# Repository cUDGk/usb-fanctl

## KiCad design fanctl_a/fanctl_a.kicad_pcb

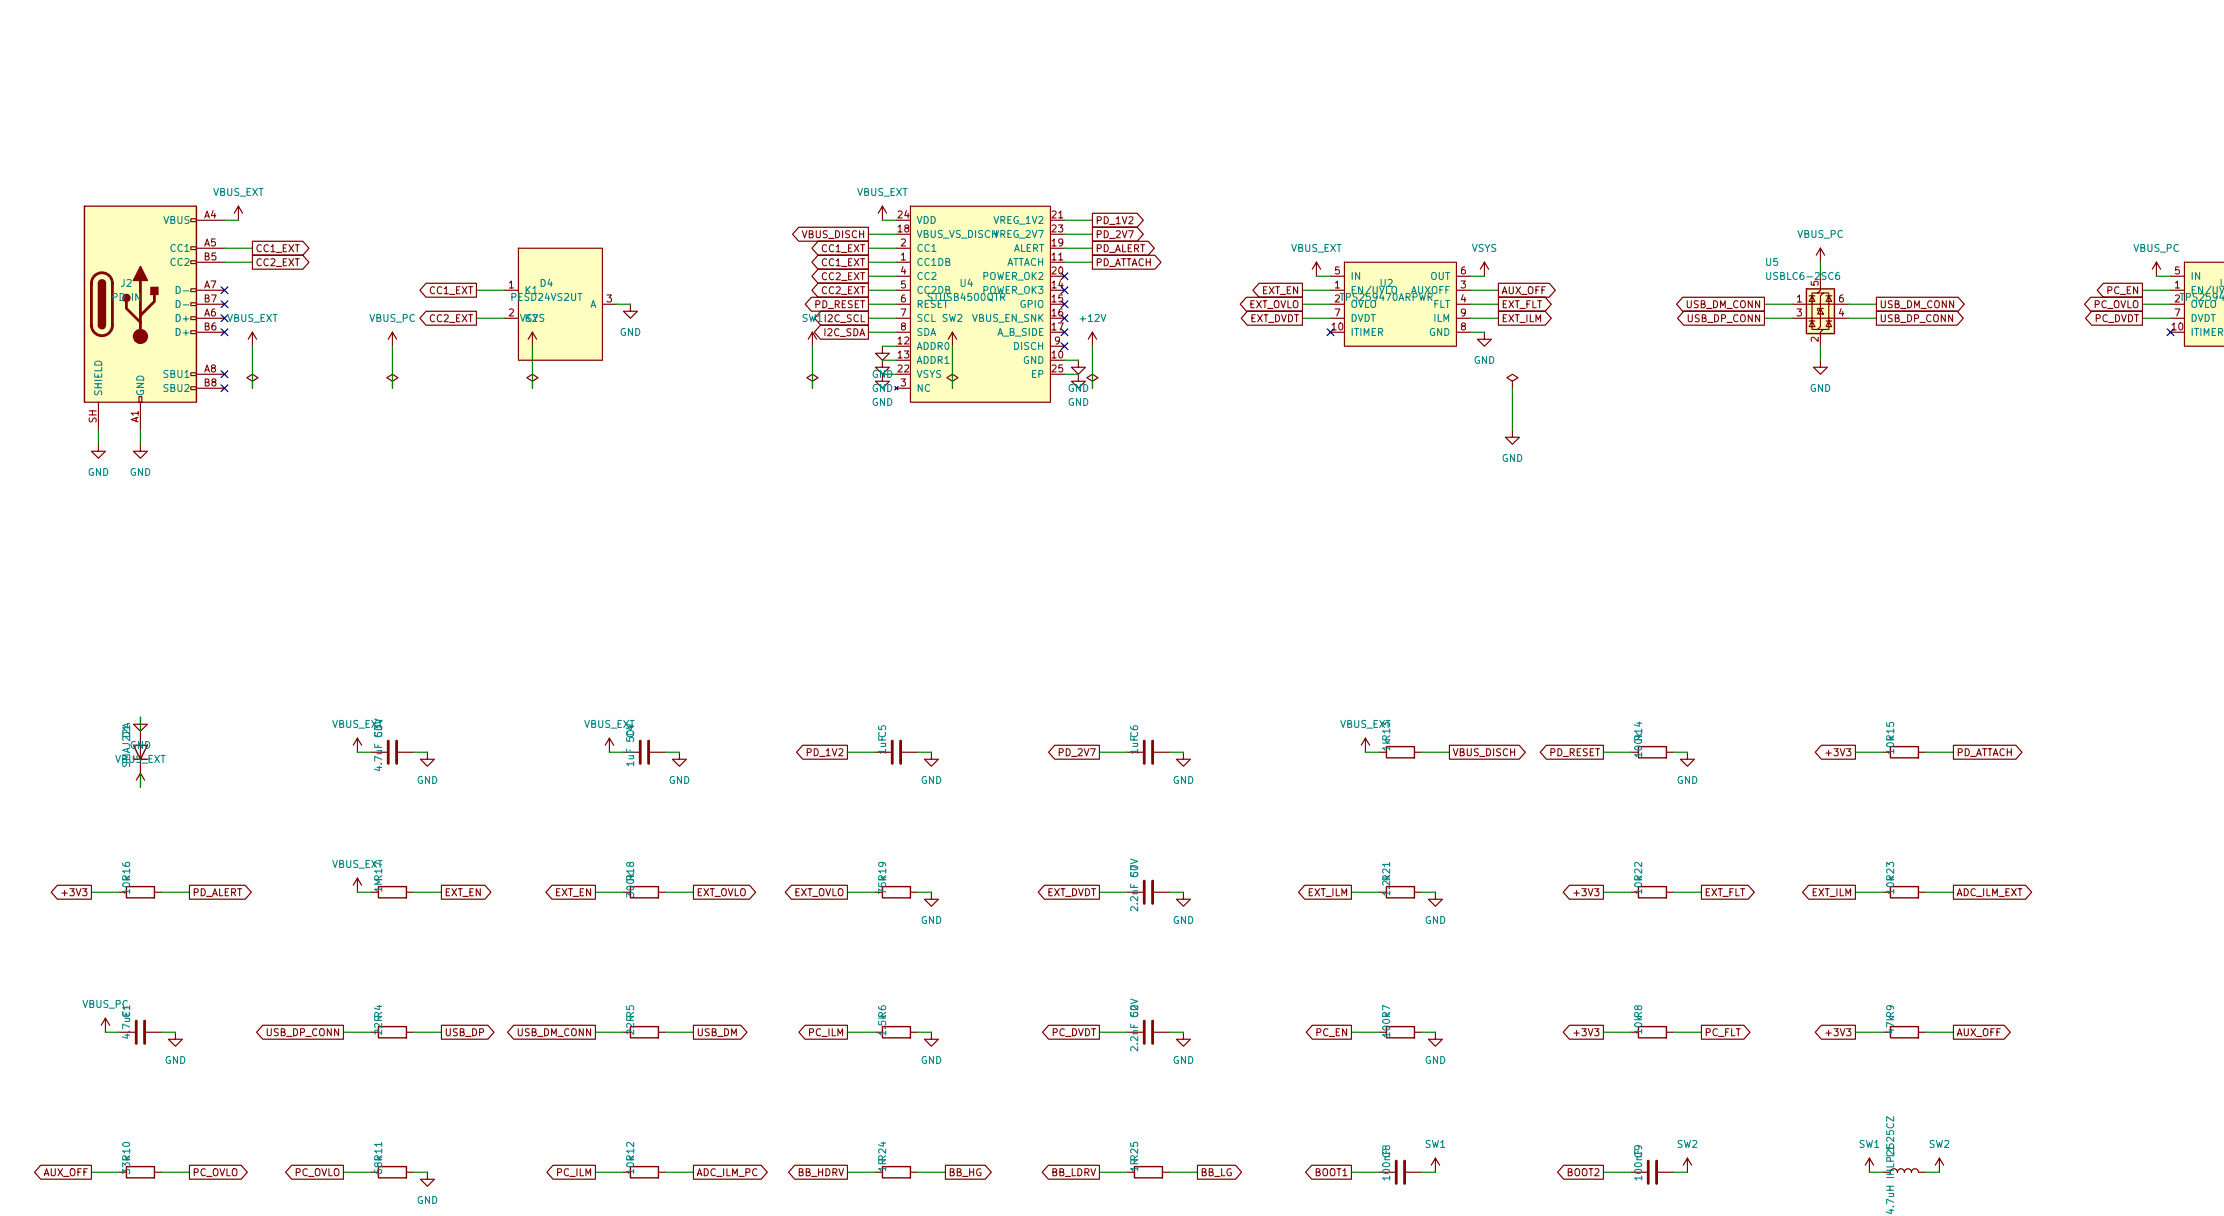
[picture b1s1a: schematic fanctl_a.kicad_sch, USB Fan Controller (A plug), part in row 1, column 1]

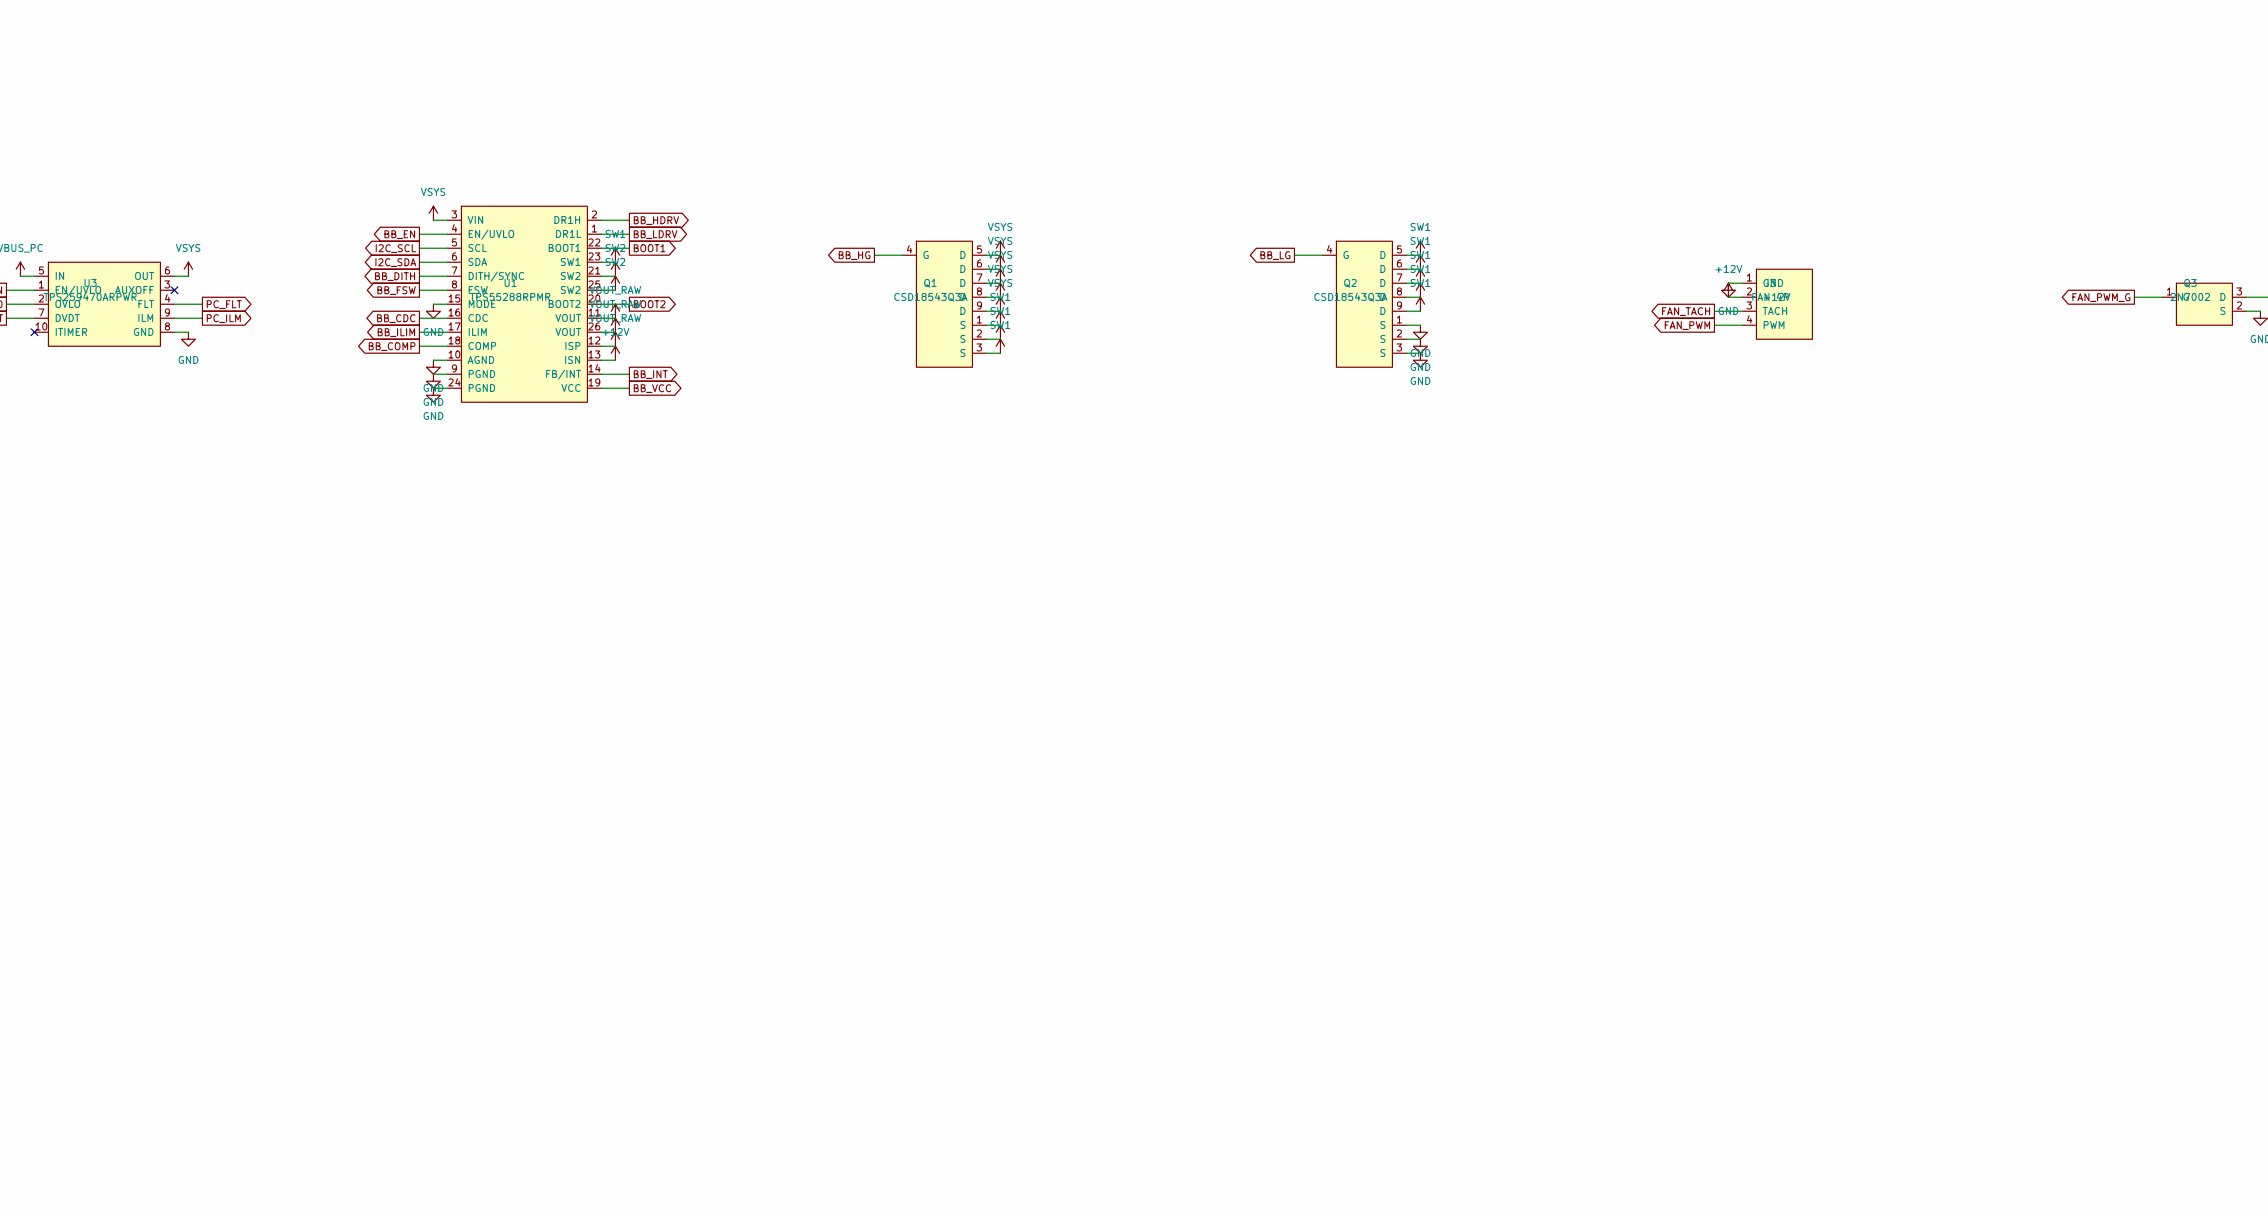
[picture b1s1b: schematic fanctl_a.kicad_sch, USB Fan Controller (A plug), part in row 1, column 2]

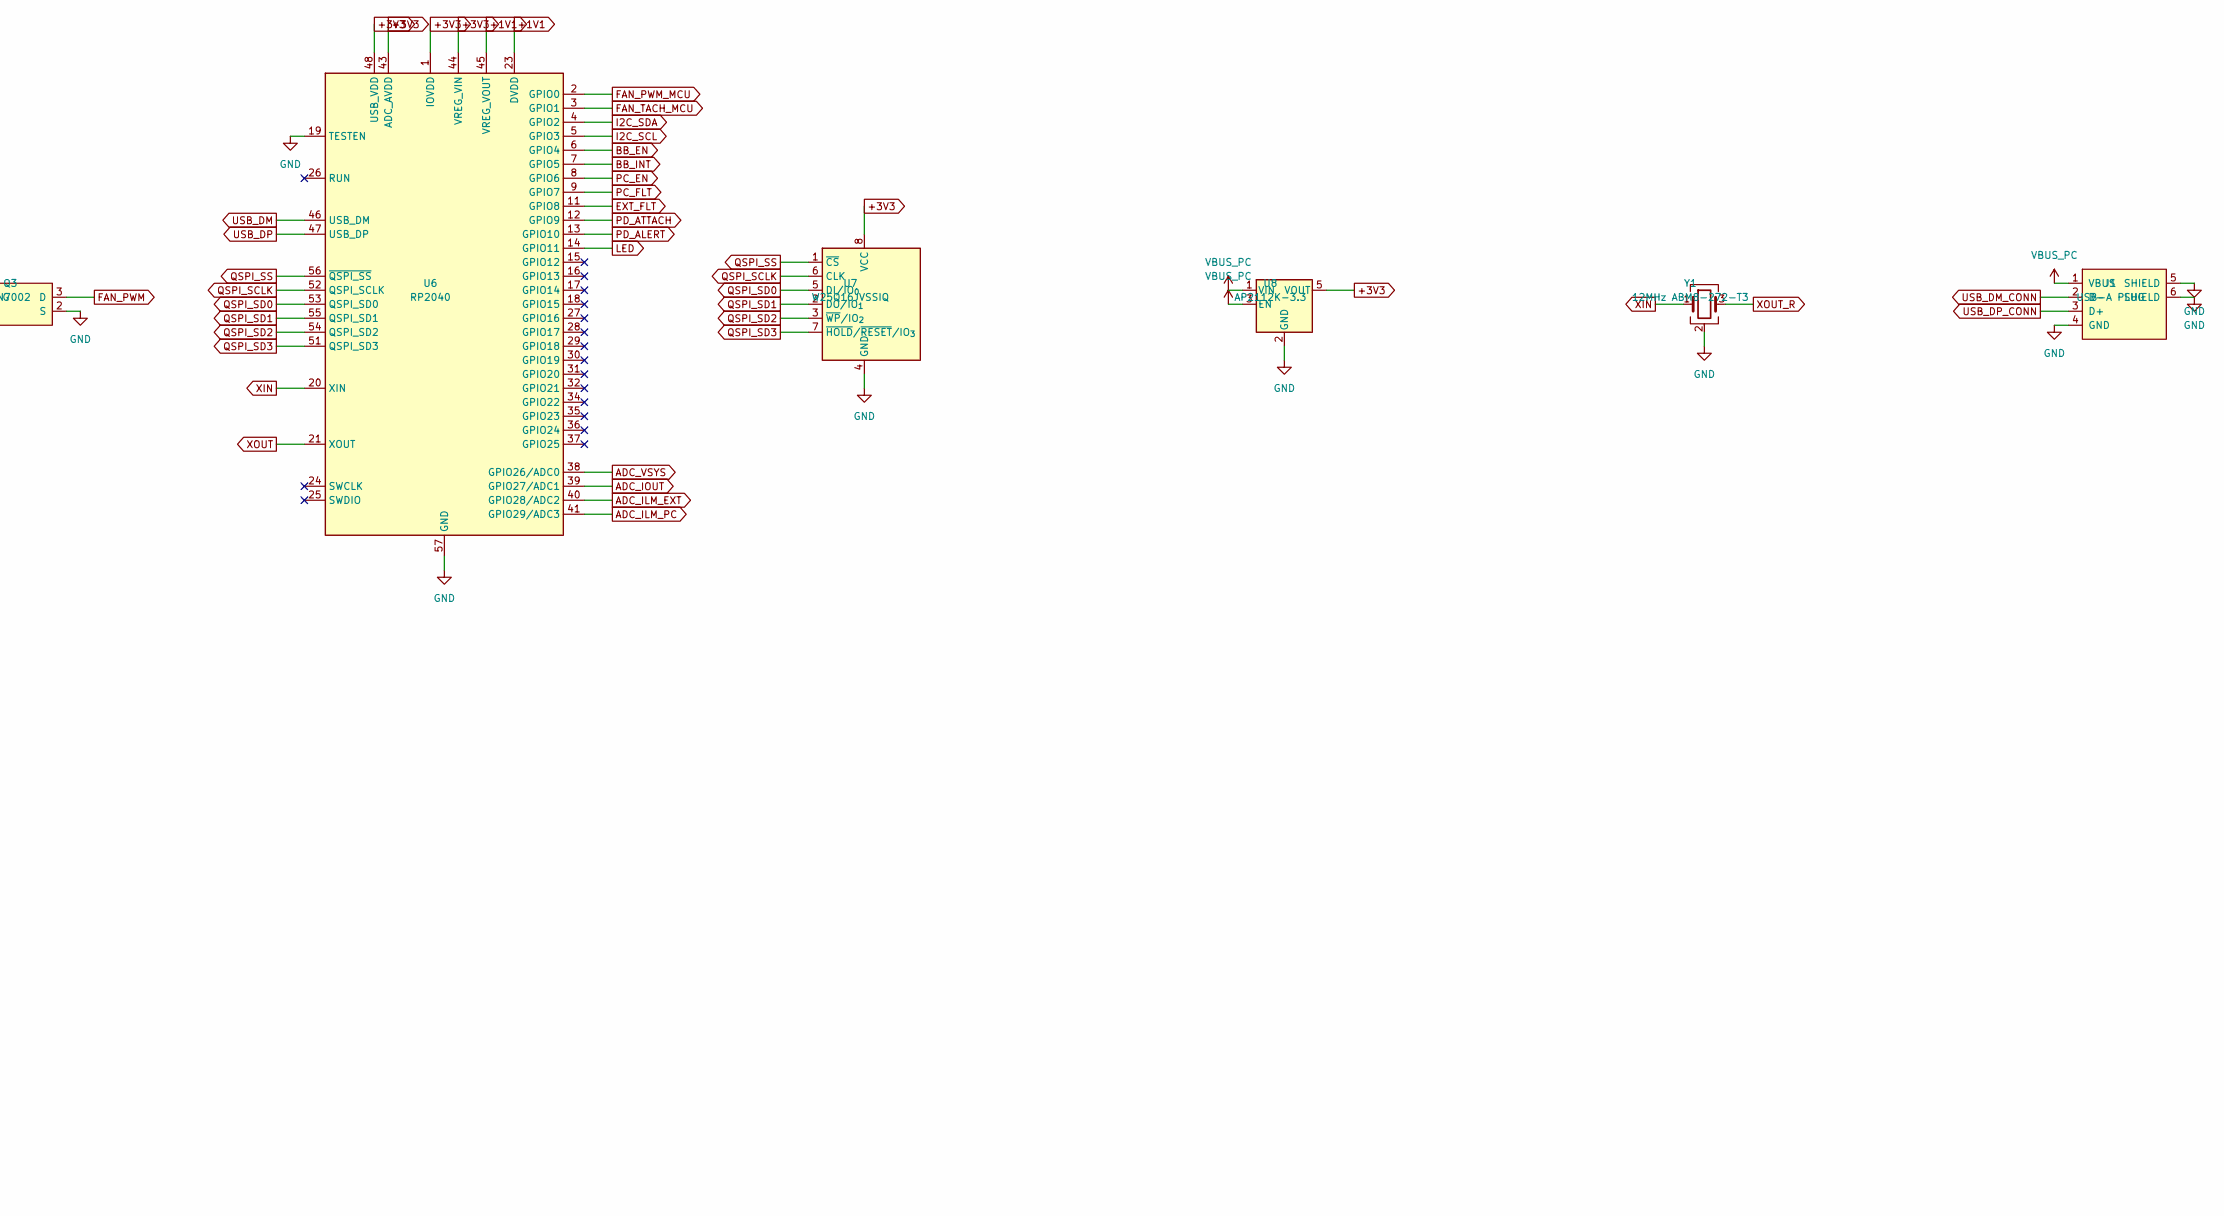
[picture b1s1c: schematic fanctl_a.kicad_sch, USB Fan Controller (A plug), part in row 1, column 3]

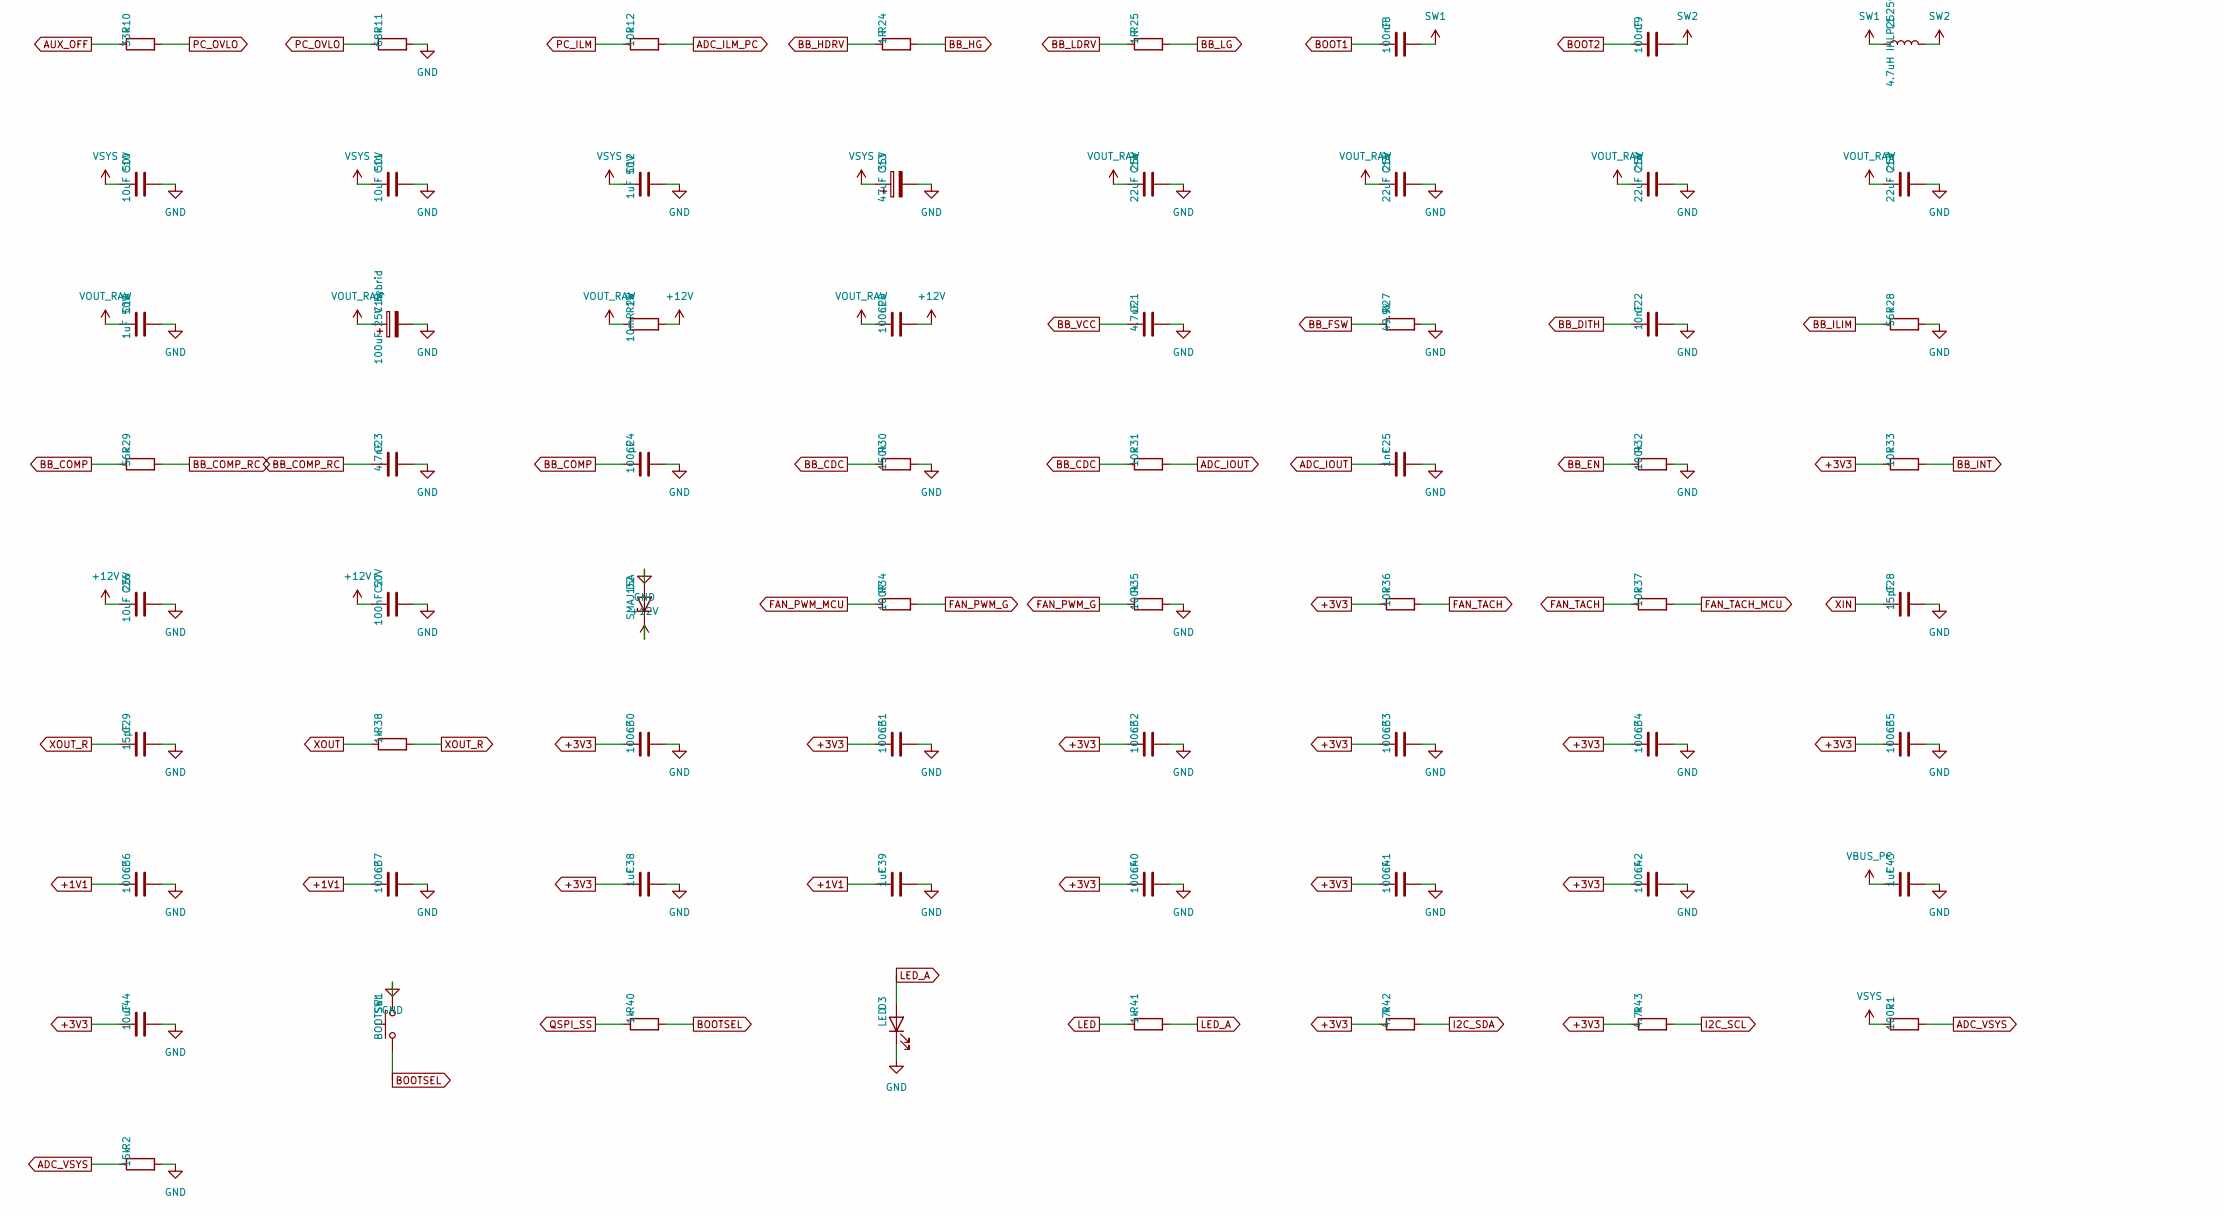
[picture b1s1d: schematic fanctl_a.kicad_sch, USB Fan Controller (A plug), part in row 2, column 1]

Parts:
C1, C21: 4.7uF; C_0603_1608Metric
C2, C7: 2.2nF 50V; C_0402_1005Metric
C3: 4.7uF 50V; C_1206_3216Metric
C4, C12, C18: 1uF 50V; C_0603_1608Metric
C5, C6, C38, C39, C43: 1uF; C_0402_1005Metric
C8, C9, C20, C30, C31, C32, C33, C34, C35, C36, C37, C40, C41, C42: 100nF; C_0402_1005Metric
C10, C11: 10uF 50V; C_1206_3216Metric
C13: 47uF 35V; CP_Elec_6.3x5.4
C14, C15, C16, C17: 22uF 25V; C_1206_3216Metric
C19: 100uF 25V hybrid; CP_Elec_6.3x5.8
C22: 10nF; C_0402_1005Metric
C23: 4.7nF; C_0402_1005Metric
C24: 100pF; C_0402_1005Metric
C25: 1nF; C_0402_1005Metric
C26: 10uF 25V; C_0805_2012Metric
C27: 100nF 50V; C_0402_1005Metric
C28, C29: 15pF; C_0402_1005Metric
C44: 10uF; C_0603_1608Metric
D1: SMAJ22A; D_SMA
D2: SMAJ15A; D_SMA
D3: LED; LED_0603_1608Metric
D4: PESD24VS2UT; SOT-23
J1: USB-A PLUG; USB-A-TH_USB2.0-A90-G
J2: PD IN; USB_C_Receptacle_HRO_TYPE-C-31-M-12
J3: FAN 4P; FanPinHeader_1x04_P2.54mm_Vertical
L1: 4.7uH IHLP2525CZ; L_Vishay_IHLP-2525
Q1, Q2: CSD18543Q3A; VSONP-8_L3.1-W3.1-P0.65-LS3.5-BL
Q3: 2N7002; SOT-23
R1, R7, R14, R32, R35: 100k; R_0402_1005Metric
R2: 15k; R_0402_1005Metric
R4, R5: 22R; R_0402_1005Metric
R6: 1.5k; R_0402_1005Metric
R8, R12, R15, R16, R22, R23, R31, R33, R36, R37: 10k; R_0402_1005Metric
R9: 47k; R_0402_1005Metric
R10: 33k; R_0402_1005Metric
R11: 68k; R_0402_1005Metric
R13: 1k; R_0805_2012Metric
R17: 1M; R_0402_1005Metric
R18: 300k; R_0402_1005Metric
R19: 75k; R_0402_1005Metric
R21: 1.2k; R_0402_1005Metric
R24, R25: 1R; R_0402_1005Metric
R26: 10mR 1W; R_1206_3216Metric
R27: 49.9k; R_0402_1005Metric
R28, R29: 56k; R_0402_1005Metric
R30: 150k; R_0402_1005Metric
R34: 100R; R_0402_1005Metric
R38, R40, R41: 1k; R_0402_1005Metric
R42, R43: 4.7k; R_0402_1005Metric
SW1: BOOTSEL; SW-SMD_4P-L5.1-W5.1-P3.70-LS6.5-TL_H1.5
U1: TPS55288RPMR; VQFN-HR-26_L4.0-W3.5_TPS55288RPMR
U2, U3: TPS259470ARPWR; VQFN-10_L2.0-W2.0-P0.45-TL
U4: STUSB4500QTR; QFN-24_L4.0-W4.0-P0.50-BL-EP2.8
U5: USBLC6-2SC6; SOT-23-6
U6: RP2040; QFN-56-1EP_7x7mm_P0.4mm_EP3.2x3.2mm
U7: W25Q16JVSSIQ; SOIC-8_5.3x5.3mm_P1.27mm
U8: AP2112K-3.3; SOT-23-5
Y1: 12MHz ABM8-272-T3; Crystal_SMD_3225-4Pin_3.2x2.5mm

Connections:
+1V1: C36.1, C37.1, C39.1, U6.23 (DVDD), U6.45 (VREG_VOUT), U6.50 (DVDD)
+3V3: C30.1, C31.1, C32.1, C33.1, C34.1, C35.1, C38.1, C40.1, C41.1, C42.1, C44.1, R8.1, R9.1, R15.1, R16.1, R22.1, R33.1, R36.1, R42.1, R43.1, U6.1 (IOVDD), U6.10 (IOVDD), U6.22 (IOVDD), U6.33 (IOVDD), U6.42 (IOVDD), U6.43 (ADC_AVDD), U6.44 (VREG_VIN), U6.48 (USB_VDD), U6.49 (IOVDD), U7.8 (VCC), U8.5 (VOUT)
+12V: C20.2, C26.1, C27.1, D2.1 (K), J3.2 (+12V), R26.2, U1.13 (ISN)
ADC_ILM_EXT: R23.2, U6.40 (GPIO28/ADC2)
ADC_ILM_PC: R12.2, U6.41 (GPIO29/ADC3)
ADC_IOUT: C25.1, R31.2, U6.39 (GPIO27/ADC1)
ADC_VSYS: R1.2, R2.1, U6.38 (GPIO26/ADC0)
AUX_OFF: R9.2, R10.1, U2.3 (AUXOFF)
BB_CDC: R30.1, R31.1, U1.16 (CDC)
BB_COMP: C24.1, R29.1, U1.18 (COMP)
BB_COMP_RC: C23.1, R29.2
BB_DITH: C22.1, U1.7 (DITH/SYNC)
BB_EN: R32.1, U1.4 (EN/UVLO), U6.6 (GPIO4)
BB_FSW: R27.1, U1.8 (FSW)
BB_HDRV: R24.1, U1.2 (DR1H)
BB_HG: Q1.4 (G), R24.2
BB_ILIM: R28.1, U1.17 (ILIM)
BB_INT: R33.2, U1.14 (FB/INT), U6.7 (GPIO5)
BB_LDRV: R25.1, U1.1 (DR1L)
BB_LG: Q2.4 (G), R25.2
BB_VCC: C21.1, U1.19 (VCC)
BOOT1: C8.1, U1.22 (BOOT1)
BOOT2: C9.1, U1.20 (BOOT2)
BOOTSEL: R40.2, SW1.1
CC1_EXT: D4.1 (K1), J2.A5 (CC1), U4.1 (CC1DB), U4.2 (CC1)
CC2_EXT: D4.2 (K2), J2.B5 (CC2), U4.4 (CC2), U4.5 (CC2DB)
EXT_DVDT: C7.1, U2.7 (DVDT)
EXT_EN: R17.2, R18.1, U2.1 (EN/UVLO)
EXT_FLT: R22.2, U2.4 (FLT), U6.11 (GPIO8)
EXT_ILM: R21.1, R23.1, U2.9 (ILM)
EXT_OVLO: R18.2, R19.1, U2.2 (OVLO)
FAN_PWM: J3.4 (PWM), Q3.3 (D)
FAN_PWM_G: Q3.1 (G), R34.2, R35.1
FAN_PWM_MCU: R34.1, U6.2 (GPIO0)
FAN_TACH: J3.3 (TACH), R36.2, R37.1
FAN_TACH_MCU: R37.2, U6.3 (GPIO1)
GND: C1.2, C2.2, C3.2, C4.2, C5.2, C6.2, C7.2, C10.2, C11.2, C12.2, C13.2, C14.2, C15.2, C16.2, C17.2, C18.2, C19.2, C21.2, C22.2, C23.2, C24.2, C25.2, C26.2, C27.2, C28.2, C29.2, C30.2, C31.2, C32.2, C33.2, C34.2, C35.2, C36.2, C37.2, C38.2, C39.2, C40.2, C41.2, C42.2, C43.2, C44.2, D1.2 (A), D2.2 (A), D3.1 (K), D4.3 (A), J1.4 (GND), J1.5 (SHIELD), J1.6 (SHIELD), J2.A1 (GND), J2.A12 (GND), J2.B1 (GND), J2.B12 (GND), J2.SH (SHIELD), J3.1 (GND), Q2.1 (S), Q2.2 (S), Q2.3 (S), Q3.2 (S), R2.2, R6.2, R7.2, R11.2, R14.2, R19.2, R21.2, R27.2, R28.2, R30.2, R32.2, R35.2, SW1.2, U1.9 (PGND), U1.10 (AGND), U1.15 (MODE), U1.24 (PGND), U2.8 (GND), U3.8 (GND), U4.10 (GND), U4.12 (ADDR0), U4.13 (ADDR1), U4.22 (VSYS), U4.25 (EP), U5.2 (GND), U6.19 (TESTEN), U6.57 (GND), U7.4 (GND), U8.2 (GND), Y1.2 (G), Y1.4 (G)
I2C_SCL: R43.2, U1.5 (SCL), U4.7 (SCL), U6.5 (GPIO3)
I2C_SDA: R42.2, U1.6 (SDA), U4.8 (SDA), U6.4 (GPIO2)
LED: R41.1, U6.14 (GPIO11)
LED_A: D3.2 (A), R41.2
PC_DVDT: C2.1, U3.7 (DVDT)
PC_EN: R7.1, U3.1 (EN/UVLO), U6.8 (GPIO6)
PC_FLT: R8.2, U3.4 (FLT), U6.9 (GPIO7)
PC_ILM: R6.1, R12.1, U3.9 (ILM)
PC_OVLO: R10.2, R11.1, U3.2 (OVLO)
PD_1V2: C5.1, U4.21 (VREG_1V2)
PD_2V7: C6.1, U4.23 (VREG_2V7)
PD_ALERT: R16.2, U4.19 (ALERT), U6.13 (GPIO10)
PD_ATTACH: R15.2, U4.11 (ATTACH), U6.12 (GPIO9)
PD_RESET: R14.1, U4.6 (RESET)
QSPI_SCLK: U6.52 (QSPI_SCLK), U7.6 (CLK)
QSPI_SD0: U6.53 (QSPI_SD0), U7.5 (DI/IO_{0})
QSPI_SD1: U6.55 (QSPI_SD1), U7.2 (DO/IO_{1})
QSPI_SD2: U6.54 (QSPI_SD2), U7.3 (~WP/IO_{2})
QSPI_SD3: U6.51 (QSPI_SD3), U7.7 (~HOLD/~RESET/IO_{3})
QSPI_SS: R40.1, U6.56 (~QSPI_SS), U7.1 (~CS)
SW1: C8.2, L1.1, Q1.1 (S), Q1.2 (S), Q1.3 (S), Q2.5 (D), Q2.6 (D), Q2.7 (D), Q2.8 (D), Q2.9 (D), U1.23 (SW1)
SW2: C9.2, L1.2, U1.21 (SW2), U1.25 (SW2)
USB_DM: R5.2, U6.46 (USB_DM)
USB_DM_CONN: J1.2 (D-), R5.1, U5.1 (I/O1), U5.6 (I/O1)
USB_DP: R4.2, U6.47 (USB_DP)
USB_DP_CONN: J1.3 (D+), R4.1, U5.3 (I/O2), U5.4 (I/O2)
VBUS_DISCH: R13.2, U4.18 (VBUS_VS_DISCH)
VBUS_EXT: C3.1, C4.1, D1.1 (K), J2.A4 (VBUS), J2.A9 (VBUS), J2.B4 (VBUS), J2.B9 (VBUS), R13.1, R17.1, U2.5 (IN), U4.24 (VDD)
VBUS_PC: C1.1, C43.1, J1.1 (VBUS), U3.5 (IN), U5.5 (VBUS), U8.1 (VIN), U8.3 (EN)
VOUT_RAW: C14.1, C15.1, C16.1, C17.1, C18.1, C19.1, C20.1, R26.1, U1.11 (VOUT), U1.12 (ISP), U1.26 (VOUT)
VSYS: C10.1, C11.1, C12.1, C13.1, Q1.5 (D), Q1.6 (D), Q1.7 (D), Q1.8 (D), Q1.9 (D), R1.1, U1.3 (VIN), U2.6 (OUT), U3.6 (OUT)
XIN: C28.1, U6.20 (XIN), Y1.1
XOUT: R38.1, U6.21 (XOUT)
XOUT_R: C29.1, R38.2, Y1.3

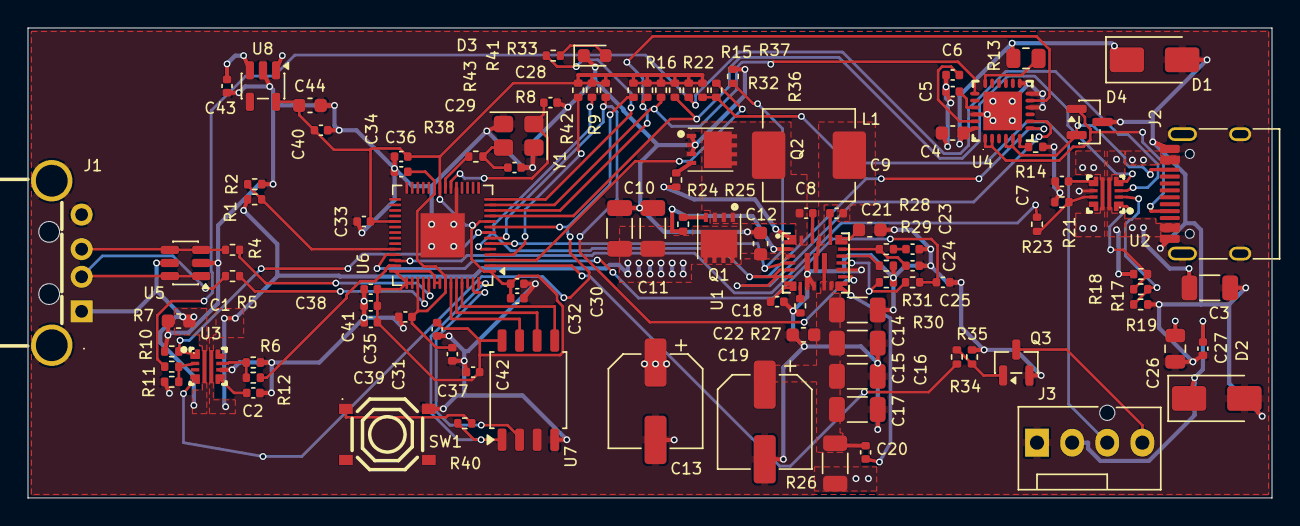
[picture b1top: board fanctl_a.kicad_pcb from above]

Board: 4 copper layers, 90.0 x 34.0 mm, 105 parts (0 on the bottom side), 71 nets.

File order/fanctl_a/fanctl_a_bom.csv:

Comment,Designator,Footprint,LCSC Part #
4.7uF,"C1,C21",C_0603_1608Metric,C19666
2.2nF 50V,"C2,C7",C_0402_1005Metric,C1531
4.7uF 50V,C3,C_1206_3216Metric,C29823
1uF 50V,"C4,C12,C18",C_0603_1608Metric,C15849
1uF,"C5,C6,C38,C39,C43",C_0402_1005Metric,C52923
100nF,"C8,C9,C20,C30,C31,C32,C33,C34,C35,C36,C37,C40,C41,C42",C_0402_1005Metric,C1525
10uF 50V,"C10,C11",C_1206_3216Metric,C13585
47uF 35V,C13,CP_Elec_6.3x5.4,C2836440
22uF 25V,"C14,C15,C16,C17",C_1206_3216Metric,C12891
100uF 25V hybrid,C19,CP_Elec_6.3x5.8,C454668
10nF,C22,C_0402_1005Metric,C15195
4.7nF,C23,C_0402_1005Metric,C1538
100pF,C24,C_0402_1005Metric,C1546
1nF,C25,C_0402_1005Metric,C1523
10uF 25V,C26,C_0805_2012Metric,C15850
100nF 50V,C27,C_0402_1005Metric,C307331
15pF,"C28,C29",C_0402_1005Metric,C1548
10uF,C44,C_0603_1608Metric,C19702
SMAJ22A,D1,D_SMA,C908773
SMAJ15A,D2,D_SMA,C908769
LED,D3,LED_0603_1608Metric,C2286
PESD24VS2UT,D4,SOT-23,C477999
USB-A PLUG,J1,USB-A-TH_USB2.0-A90-G,C53699947
PD IN,J2,USB_C_Receptacle_HRO_TYPE-C-31-M-12,C165948
FAN 4P,J3,FanPinHeader_1x04_P2.54mm_Vertical,C240840
4.7uH IHLP2525CZ,L1,L_Vishay_IHLP-2525,C553961
CSD18543Q3A,"Q1,Q2",VSONP-8_L3.1-W3.1-P0.65-LS3.5-BL,C840100
2N7002,Q3,SOT-23,C8545
100k,"R1,R7,R14,R32,R35",R_0402_1005Metric,C25741
15k,R2,R_0402_1005Metric,C25756
22R,"R4,R5",R_0402_1005Metric,C25092
1.5k,R6,R_0402_1005Metric,C25867
10k,"R8,R12,R15,R16,R22,R23,R31,R33,R36,R37",R_0402_1005Metric,C25744
47k,R9,R_0402_1005Metric,C25792
33k,R10,R_0402_1005Metric,C25779
68k,R11,R_0402_1005Metric,C36871
1k,R13,R_0805_2012Metric,C17513
1M,R17,R_0402_1005Metric,C26083
300k,R18,R_0402_1005Metric,C25774
75k,R19,R_0402_1005Metric,C25798
1.2k,R21,R_0402_1005Metric,C25862
1R,"R24,R25",R_0402_1005Metric,C25086
10mR 1W,R26,R_1206_3216Metric,C105362
49.9k,R27,R_0402_1005Metric,C25897
56k,"R28,R29",R_0402_1005Metric,C25796
150k,R30,R_0402_1005Metric,C25755
100R,R34,R_0402_1005Metric,C25076
1k,"R38,R40,R41",R_0402_1005Metric,C11702
4.7k,"R42,R43",R_0402_1005Metric,C25900
BOOTSEL,SW1,SW-SMD_4P-L5.1-W5.1-P3.70-LS6.5-TL_H1.5,C318884
TPS55288RPMR,U1,VQFN-HR-26_L4.0-W3.5_TPS55288RPMR,C2864583
TPS259470ARPWR,"U2,U3",VQFN-10_L2.0-W2.0-P0.45-TL,C3662799
STUSB4500QTR,U4,QFN-24_L4.0-W4.0-P0.50-BL-EP2.8,C2678061
USBLC6-2SC6,U5,SOT-23-6,C7519
RP2040,U6,QFN-56-1EP_7x7mm_P0.4mm_EP3.2x3.2mm,C2040
W25Q16JVSSIQ,U7,SOIC-8_5.3x5.3mm_P1.27mm,C131025
AP2112K-3.3,U8,SOT-23-5,C51118
12MHz ABM8-272-T3,Y1,Crystal_SMD_3225-4Pin_3.2x2.5mm,C20625731

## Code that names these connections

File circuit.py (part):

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        ("PD_1V2", False, [("U4", "21"), ("C5", "1")]),
        ("PD_2V7", False, [("U4", "23"), ("C6", "1")]),
        ("PD_RESET", False, [("U4", "6"), ("R14", "1")]),
        ("PD_ATTACH", False, [("U4", "11"), ("R15", "2"), ("U6", "name:GPIO9")]),
        ("PD_ALERT", False, [("U4", "19"), ("R16", "2"), ("U6", "name:GPIO10")]),
        ("EXT_EN", False, [("U2", "1"), ("R17", "2"), ("R18", "1")]),
        ("EXT_OVLO", False, [("U2", "2"), ("R18", "2"), ("R19", "1")]),
        ("EXT_DVDT", False, [("U2", "7"), ("C7", "1")]),
        ("EXT_ILM", False, [("U2", "9"), ("R21", "1"), ("R23", "1")]),
        ("ADC_ILM_EXT", False, [("R23", "2"), ("U6", "name:GPIO28/ADC2")]),
        ("EXT_FLT", False, [("U2", "4"), ("R22", "2"), ("U6", "name:GPIO8")]),
        ("AUX_OFF", False, [("U2", "3"), ("R9", "2"), ("R10", "1")]),
        ("PC_OVLO", False, [("U3", "2"), ("R10", "2"), ("R11", "1")]),
        # PC 側
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        ("USB_DP_CONN", False, [("J1", "name:D+"), ("U5", "3"), ("U5", "4"), ("R4", "1")]),
        ("USB_DP", False, [("R4", "2"), ("U6", "name:USB_DP")]),
        ("USB_DM", False, [("R5", "2"), ("U6", "name:USB_DM")]),
        ("PC_EN", False, [("U3", "1"), ("R7", "1"), ("U6", "name:GPIO6")]),
        ("PC_FLT", False, [("U3", "4"), ("R8", "2"), ("U6", "name:GPIO7")]),
        ("PC_DVDT", False, [("U3", "7"), ("C2", "1")]),
        ("PC_ILM", False, [("U3", "9"), ("R6", "1"), ("R12", "1")]),
        ("ADC_ILM_PC", False, [("R12", "2"), ("U6", "name:GPIO29/ADC3")]),
        # コンバータ
        ("BB_HDRV", False, [("U1", "2"), ("R24", "1")]),
        ("BB_HG", False, [("R24", "2"), ("Q1", "name:G")]),
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        ("BB_COMP", False, [("U1", "18"), ("R29", "1"), ("C24", "1")]),
        ("BB_COMP_RC", False, [("R29", "2"), ("C23", "1")]),
        ("BB_CDC", False, [("U1", "16"), ("R30", "1"), ("R31", "1")]),
        ("ADC_IOUT", False, [("R31", "2"), ("C25", "1"), ("U6", "name:GPIO27/ADC1")]),
        ("BB_EN", False, [("U1", "4"), ("R32", "1"), ("U6", "name:GPIO4")]),
        ("BB_INT", False, [("U1", "14"), ("R33", "2"), ("U6", "name:GPIO5")]),
        ("I2C_SDA", False, [("U1", "6"), ("U4", "8"), ("R42", "2"), ("U6", "name:GPIO2")]),
        ("I2C_SCL", False, [("U1", "5"), ("U4", "7"), ("R43", "2"), ("U6", "name:GPIO3")]),
        # ファン
        ("FAN_PWM_MCU", False, [("U6", "name:GPIO0"), ("R34", "1")]),
        ("FAN_PWM_G", False, [("R34", "2"), ("R35", "1"), ("Q3", "1")]),
        ("FAN_PWM", False, [("Q3", "3"), ("J3", "4")]),
        ("FAN_TACH", False, [("J3", "3"), ("R36", "2"), ("R37", "1")]),
        ("FAN_TACH_MCU", False, [("R37", "2"), ("U6", "name:GPIO1")]),
        # MCU 周辺
        ("XIN", False, [("U6", "name:XIN"), ("Y1", "1"), ("C28", "1")]),
        ("XOUT", False, [("U6", "name:XOUT"), ("R38", "1")]),
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        ("QSPI_SD1", False, [("U6", "name:QSPI_SD1"), ("U7", "2")]),
        ("QSPI_SD2", False, [("U6", "name:QSPI_SD2"), ("U7", "3")]),
        ("QSPI_SD3", False, [("U6", "name:QSPI_SD3"), ("U7", "7")]),
        ("LED", False, [("U6", "name:GPIO11"), ("R41", "1")]),
        ("LED_A", False, [("R41", "2"), ("D3", "2")]),
    ]

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        nets = [
            # CC の電圧で PC ポートの供給能力 (Default/1.5A/3A) を判定する
            ("CC_PC", False, [("J1", "A5"), ("R1", "1"), ("R2", "1")]),
            ("ADC_CC", False, [("R2", "2"), ("U6", "name:GPIO26/ADC0")]),
            ("GND", True, [("J1", "name:GND"), ("J1", "name:SHIELD"), ("R1", "2")]),
        ]
    elif kind == "a":
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        ]
        nets = [
            ("VSYS", True, [("R1", "1")]),
            ("ADC_VSYS", False, [("R1", "2"), ("R2", "1"), ("U6", "name:GPIO26/ADC0")]),
            ("GND", True, [("J1", "name:GND"), ("J1", "name:SHIELD"), ("R2", "2")]),
        ]
    else:
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
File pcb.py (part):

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    L.routes.append(("GND", "F", 0.2, [L.pad("U1", "15"), (160.3, 117.5)]))
    L.routes.append(("BB_ILIM", "F", 0.2, [L.pad("U1", "17"), (160.9, 116.5), L.pad("R28", "1")]))
    L.routes.append(("BB_INT", "F", 0.2, [L.pad("U1", "14"), (159.6, 118.0), (159.75, 118.25)]))
    # BB_EN (MCU GPIO4 → U1 EN) は電源段の下を裏面で一直線に渡す
    en_a, en_b = (135.2, 115.6), (153.3, 117.4)
    L.routes.append(("BB_EN", "F", 0.2, [L.pad("U6", "6"), en_a]))
    L.routes.append(("BB_EN", "B", 0.2, [en_a, (152.8, 115.6), en_b]))
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    L.routes.append(("GND", "F", 0.25, [L.pad("U6", "19"), (131.0, 113.6)]))
    L.routes.append(("+3V3", "F", 0.25, [L.pad("C30", "1"), L.pad("C32", "1")]))
    # QSPI の上段 3 本 (SD3/SCLK/SD0) は入れ子で決め打ち。右ほど高い位置で曲げて交差を避ける
    for net, mcu_pin, flash_pin, y in (("QSPI_SD3", "51", "7", 121.05), ("QSPI_SCLK", "52", "6", 120.6),
                                       ("QSPI_SD0", "53", "5", 120.15)):
        mx, my = L.pad("U6", mcu_pin)
        fx, fy = L.pad("U7", flash_pin)
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    L.stub("VBUS_EXT", "R13", "1", (171.2, 101.1))
    L.routes.append(("EXT_DVDT", "F", 0.2, [L.pad("C7", "1"), L.pad("U2", "7")]))
    # U2 右側 (J2 側) の信号ピンは VBUS ポリゴンに挟まれるので、決め打ちのビアで裏面へ逃がす
    for net, pin, via in (("EXT_FLT", "4", (179.9, 110.55)), ("AUX_OFF", "3", (179.95, 111.55)),
                          ("EXT_OVLO", "2", (180.35, 112.35)), ("EXT_EN", "1", (179.75, 113.25))):
        pad = L.pad("U2", pin)
        L.routes.append((net, "F", 0.2, [pad, (179.5, pad[1]), via]))
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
